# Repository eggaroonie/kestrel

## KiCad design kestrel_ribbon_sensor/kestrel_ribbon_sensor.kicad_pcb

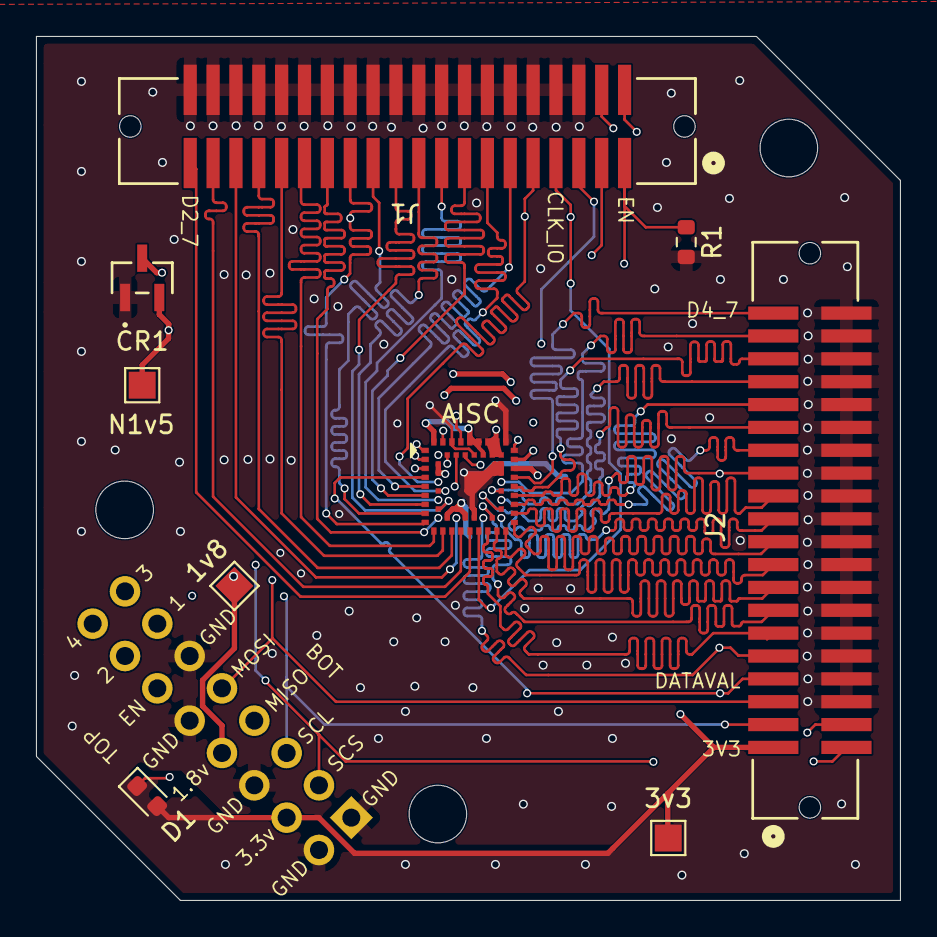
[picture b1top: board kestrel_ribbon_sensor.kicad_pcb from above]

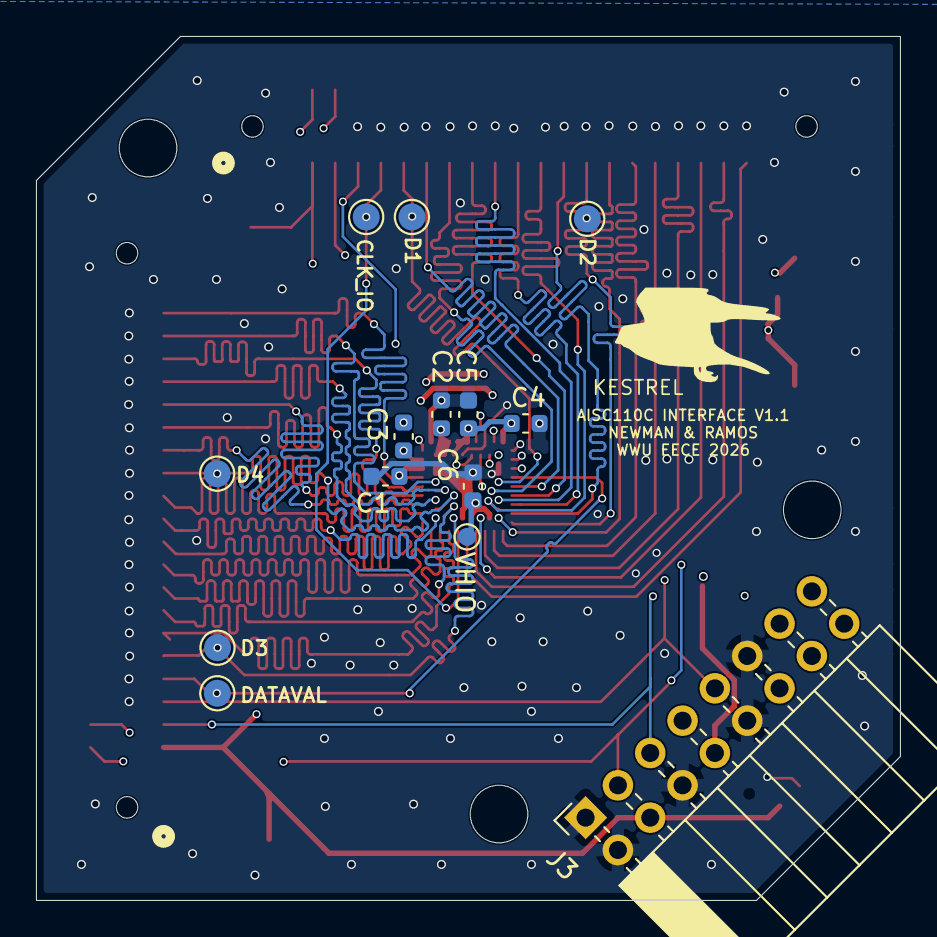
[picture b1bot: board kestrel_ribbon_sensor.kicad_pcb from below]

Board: 4 copper layers, 48.0 x 48.0 mm, 26 parts (14 on the bottom side), 51 nets.

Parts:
1v8: V1V8_PWR; TestPoint_Pad_1.5x1.5mm
3v3: V3V3_PWR; TestPoint_Pad_1.5x1.5mm
AISC: AISC110C
C1: 1uF; C_0603_1608Metric
C2, C4, C5, C6: 2.2uF; C_0603_1608Metric
C3: 220nF; C_0603_1608Metric
CLK_IO: CLK_IO; TestPoint_Pad_D1.5mm
CR1: BAS40-04-E3-08; SOT_04-HE3-08_VIS-M
D1: LED; LED_0603_1608Metric
D1#2: D1_0; TestPoint_Pad_D1.5mm
D2: D2_0; TestPoint_Pad_D1.5mm
D3: D3_0; TestPoint_Pad_D1.5mm
D4: D4_0; TestPoint_Pad_D1.5mm
DATAVAL: DATAVALID; TestPoint_Pad_D1.5mm
H1, H2, H3: MountingHole; MountingHole_3.2mm_M3
J1, J2: SHF-120-01-L-D-SM; CONN_SHF-120-01-L-D-SM_SAI
J3: DEBUG_HEADER; PinSocket_2x08_P2.54mm_Horizontal
N1v5: VN1V5_PWR; TestPoint_Pad_1.5x1.5mm
R1: 10kR; R_0603_1608Metric
VHIO: VDD_HSIO; TestPoint_Pad_D1.0mm

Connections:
/CLK_IO: AISC.23 (CLK_IO), CLK_IO.1 (1_1), J1.7
/D1_0: AISC.13 (OUT1_0), D1#2.1 (1_1), J1.9
/D1_1: AISC.5 (OUT1_1), J1.11
/D1_2: AISC.14 (OUT1_2), J1.13
/D1_3: AISC.6 (OUT1_3), J1.15
/D1_4: AISC.15 (OUT1_4), J1.17
/D1_5: AISC.7 (OUT1_5), J1.19
/D1_6: AISC.16 (OUT1_6), J1.21
/D1_7: AISC.8 (OUT1_7), J1.23
/D2_0: AISC.9 (OUT2_0), D2.1 (1_1), J1.25
/D2_1: AISC.17 (OUT2_1), J1.27
/D2_2: AISC.18 (OUT2_2), J1.29
/D2_3: AISC.19 (OUT2_3), J1.31
/D2_4: AISC.20 (OUT2_4), J1.33
/D2_5: AISC.28 (OUT2_5), J1.35
/D2_6: AISC.21 (OUT2_6), J1.37
/D2_7: AISC.22 (OUT2_7), J1.39
/D3_0: AISC.31 (OUT3_0), D3.1 (1_1), J2.9
/D3_1: AISC.24 (OUT3_1), J2.11
/D3_2: AISC.32 (OUT3_2), J2.13
/D3_3: AISC.25 (OUT3_3), J2.15
/D3_4: AISC.26 (OUT3_4), J2.17
/D3_5: AISC.33 (OUT3_5), J2.19
/D3_6: AISC.42 (OUT3_6), J2.21
/D3_7: AISC.34 (OUT3_7), J2.23
/D4_0: AISC.43 (OUT4_0), D4.1 (1_1), J2.25
/D4_1: AISC.35 (OUT4_1), J2.27
/D4_2: AISC.44 (OUT4_2), J2.29
/D4_3: AISC.36 (OUT4_3), J2.31
/D4_4: AISC.45 (OUT4_4), J2.33
/D4_5: AISC.37 (OUT4_5), J2.35
/D4_6: AISC.46 (OUT4_6), J2.37
/D4_7: AISC.38 (OUT4_7), J2.39
/DATAVAL: AISC.4 (DATAVAL), DATAVAL.1 (1_1), J2.7
/ENABLE: AISC.57 (ENABLE), J1.1, J3.12, R1.1
/GPIO1: AISC.64 (GPIO1), J1.2, J3.13
/GPIO2: AISC.63 (GPIO2), J1.3, J3.14
/GPIO3: AISC.55 (GPIO3), J1.4, J3.15
/GPIO4: AISC.62 (GPIO4), J1.5, J3.16
/SPI_CLK: AISC.3 (SPI_CLK), J2.3, J3.5
/SPI_CS: AISC.1 (~SPI_CS), J2.2, J3.3
/SPI_MISO: AISC.10 (SPI_MISO), J2.4, J3.7
/SPI_MOSI: AISC.2 (SPI_MOSI), J2.5, J3.9
/V1V8: 1v8.1 (1_1), AISC.53 (V1V8_D), AISC.54 (IMG_V1V8), AISC.58 (VDDIO), AISC.60 (V1V8), C4.1, C5.1, J3.8
/V3V3: 3v3.1 (1_1), AISC.49 (LED_V3V3), AISC.51 (V3V3), AISC.52 (V1V8_M), AISC.59 (V3V3), C2.1, D1.2 (A), J2.1, J3.4
/VDDHSIO: AISC.27 (VDDHSIO), AISC.29 (VDDHSIO), C6.1, VHIO.1 (1_1)
GND: AISC.11 (GND), AISC.12 (GND_IO), AISC.30 (GND_IO), AISC.47 (GND_IO), AISC.48 (GND), AISC.50 (LED_PGND), AISC.56 (FTM), AISC.61 (GND), C1.2, C2.2, C4.2, C5.2, C6.2, CR1.1, J1.6, J1.8, J1.10, J1.12, J1.14, J1.16, J1.18, J1.20, J1.22, J1.24, J1.26, J1.28, J1.30, J1.32, J1.34, J1.36, J1.38, J1.40, J2.6, J2.8, J2.10, J2.12, J2.14, J2.16, J2.18, J2.20, J2.22, J2.24, J2.26, J2.28, J2.30, J2.32, J2.34, J2.36, J2.38, J2.40, J3.1, J3.2, J3.6, J3.10, J3.11, R1.2
unnamed: C3.1, CR1.3
unnamed: AISC.41 (LED_K), D1.1 (K)
unnamed: AISC.40 (CP_SW), C3.2
unnamed: AISC.39 (VN1V5), C1.1, CR1.2, N1v5.1 (1_1)

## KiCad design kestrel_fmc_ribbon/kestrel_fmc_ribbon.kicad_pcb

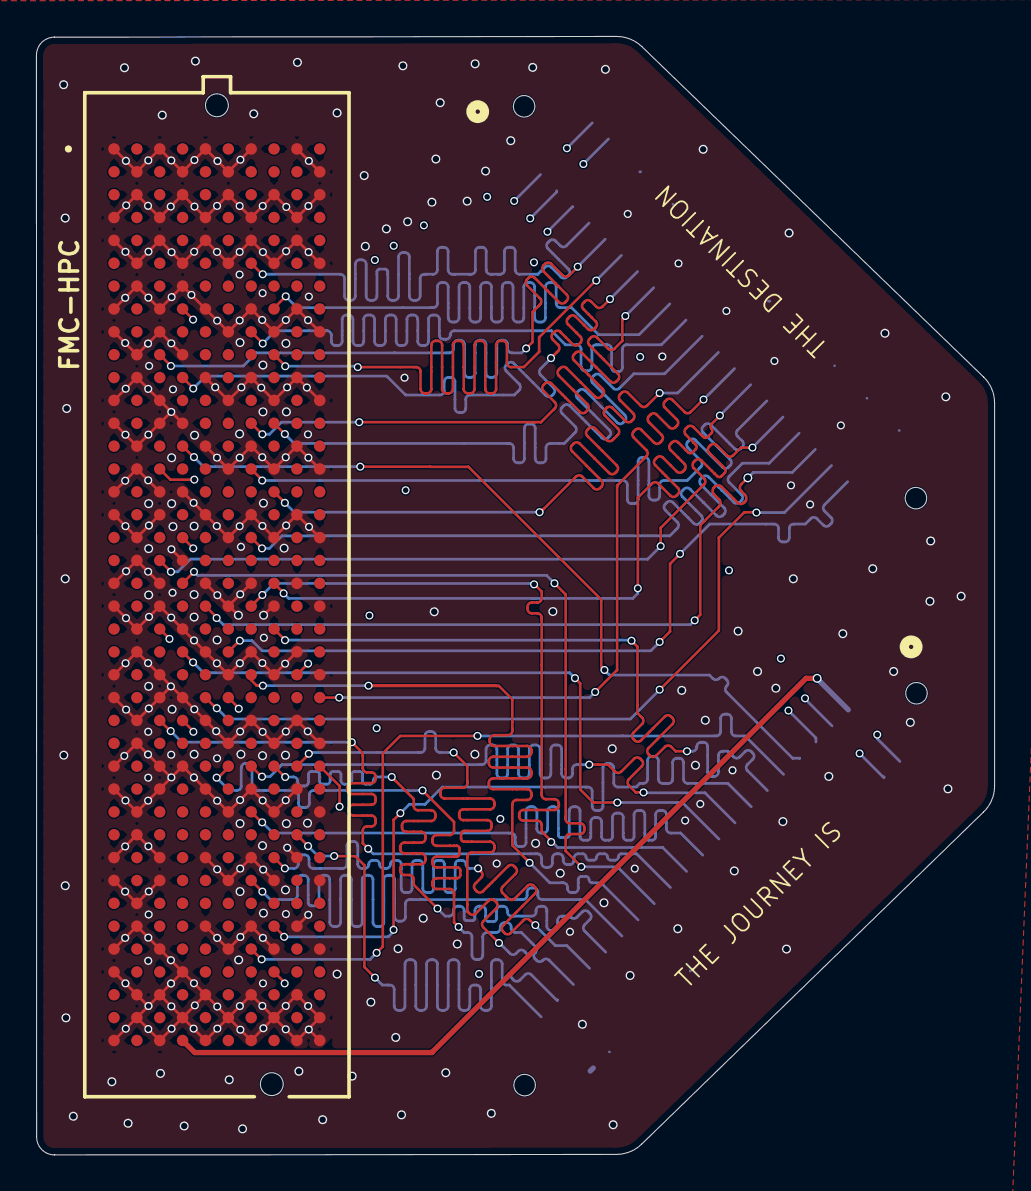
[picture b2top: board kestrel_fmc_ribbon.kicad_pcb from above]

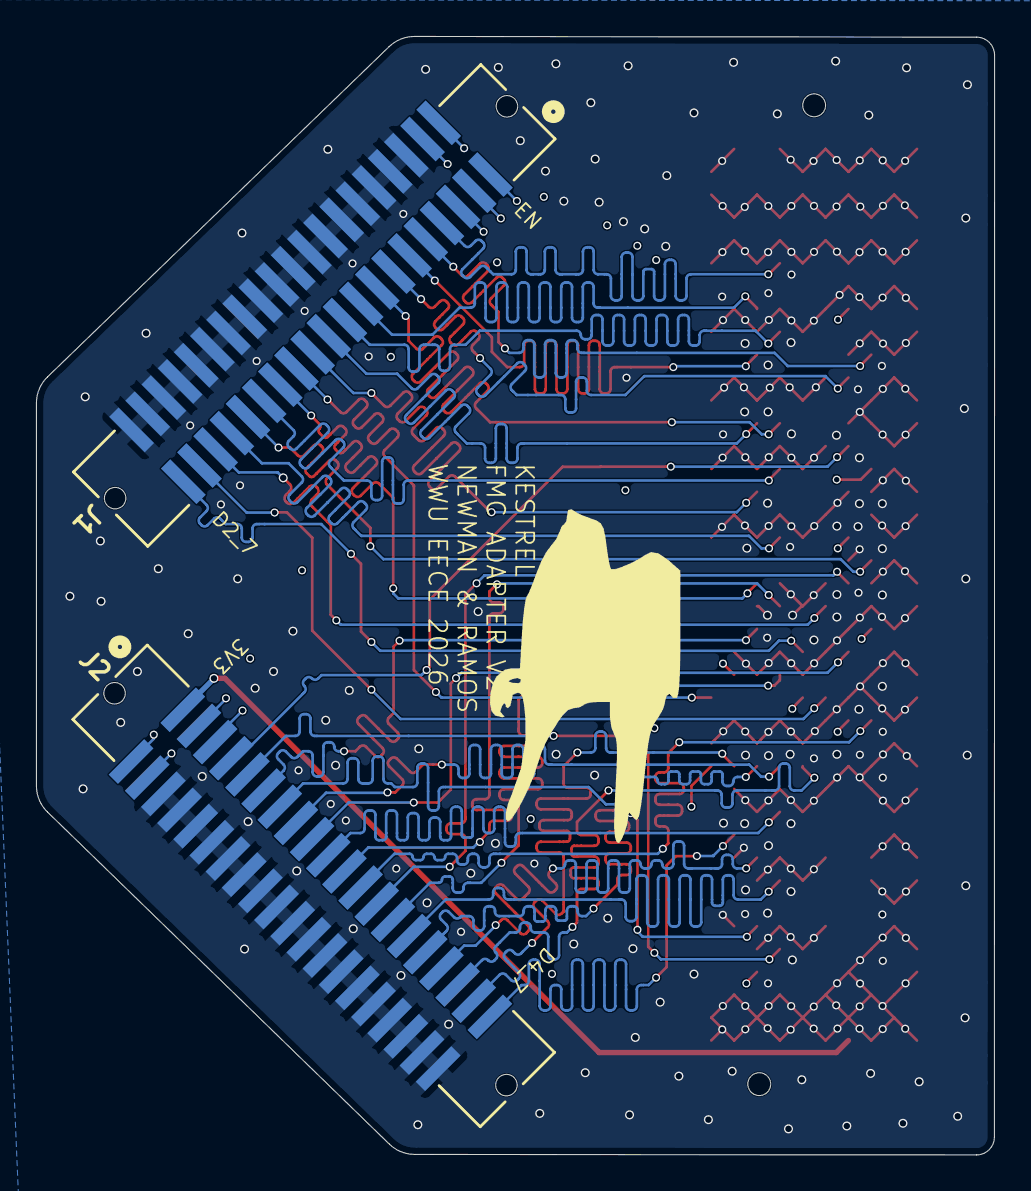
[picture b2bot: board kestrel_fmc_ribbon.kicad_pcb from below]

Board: 4 copper layers, 53.2 x 62.1 mm, 3 parts (2 on the bottom side), 45 nets.

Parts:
FMC-HPC: ASP-134602-01; SAMTEC_ASP-134602-01
J1, J2: SHF-120-01-L-D-SM; CONN_SHF-120-01-L-D-SM_SAI

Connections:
/CLK_IO: FMC-HPC.G6, J1.7
/D1_0: FMC-HPC.C10, J1.9
/D1_1: FMC-HPC.H10, J1.11
/D1_2: FMC-HPC.D11, J1.13
/D1_3: FMC-HPC.G13, J1.15
/D1_4: FMC-HPC.H8, J1.17
/D1_5: FMC-HPC.G9, J1.19
/D1_6: FMC-HPC.H13, J1.21
/D1_7: FMC-HPC.H16, J1.23
/D2_0: FMC-HPC.K25, J1.25
/D2_1: FMC-HPC.H20, J1.27
/D2_2: FMC-HPC.G15, J1.29
/D2_3: FMC-HPC.C19, J1.31
/D2_4: FMC-HPC.G18, J1.33
/D2_5: FMC-HPC.E21, J1.35
/D2_6: FMC-HPC.E25, J1.37
/D2_7: FMC-HPC.F23, J1.39
/D3_0: FMC-HPC.G36, J2.9
/D3_1: FMC-HPC.H22, J2.11
/D3_2: FMC-HPC.H35, J2.13
/D3_3: FMC-HPC.G28, J2.15
/D3_4: FMC-HPC.D23, J2.17
/D3_5: FMC-HPC.G30, J2.19
/D3_6: FMC-HPC.G21, J2.21
/D3_7: FMC-HPC.C26, J2.23
/D4_0: FMC-HPC.D20, J2.25
/D4_1: FMC-HPC.G24, J2.27
/D4_2: FMC-HPC.G33, J2.29
/D4_3: FMC-HPC.H28, J2.31
/D4_4: FMC-HPC.H32, J2.33
/D4_5: FMC-HPC.F28, J2.35
/D4_6: FMC-HPC.J28, J2.37
/D4_7: FMC-HPC.J31, J2.39
/DATAVAL: FMC-HPC.D14, J2.7
/ENABLE: FMC-HPC.C15, J1.1
/GPIO1: FMC-HPC.H37, J1.2
/GPIO2: FMC-HPC.D26, J1.3
/GPIO3: FMC-HPC.K28, J1.4
/GPIO4: FMC-HPC.C22, J1.5
/SPI_CLK: FMC-HPC.D18, J2.3
/SPI_CS: FMC-HPC.D8, J2.2
/SPI_MISO: FMC-HPC.J24, J2.4
/SPI_MOSI: FMC-HPC.F25, J2.5
/V3V3: FMC-HPC.D40, J2.1
GND: FMC-HPC.A1, FMC-HPC.A4, FMC-HPC.A5, FMC-HPC.A8, FMC-HPC.A9, FMC-HPC.A12, FMC-HPC.A13, FMC-HPC.A16, FMC-HPC.A17, FMC-HPC.A20, FMC-HPC.A21, FMC-HPC.A24, FMC-HPC.A25, FMC-HPC.A28, FMC-HPC.A29, FMC-HPC.A32, FMC-HPC.A33, FMC-HPC.A36, FMC-HPC.A37, FMC-HPC.A40, FMC-HPC.B2, FMC-HPC.B3, FMC-HPC.B6, FMC-HPC.B7, FMC-HPC.B10, FMC-HPC.B11, FMC-HPC.B14, FMC-HPC.B15, FMC-HPC.B18, FMC-HPC.B19, FMC-HPC.B22, FMC-HPC.B23, FMC-HPC.B26, FMC-HPC.B27, FMC-HPC.B30, FMC-HPC.B31, FMC-HPC.B34, FMC-HPC.B35, FMC-HPC.B38, FMC-HPC.B39, FMC-HPC.C1, FMC-HPC.C4, FMC-HPC.C5, FMC-HPC.C8, FMC-HPC.C9, FMC-HPC.C12, FMC-HPC.C13, FMC-HPC.C16, FMC-HPC.C17, FMC-HPC.C20, FMC-HPC.C21, FMC-HPC.C24, FMC-HPC.C25, FMC-HPC.C28, FMC-HPC.C29, FMC-HPC.C32, FMC-HPC.C33, FMC-HPC.C36, FMC-HPC.C38, FMC-HPC.C40, FMC-HPC.D2, FMC-HPC.D3, FMC-HPC.D6, FMC-HPC.D7, FMC-HPC.D10, FMC-HPC.D13, FMC-HPC.D16, FMC-HPC.D19, FMC-HPC.D22, FMC-HPC.D25, FMC-HPC.D28, FMC-HPC.D37, FMC-HPC.D39, FMC-HPC.E1, FMC-HPC.E4, FMC-HPC.E5, FMC-HPC.E8, FMC-HPC.E11, FMC-HPC.E14, FMC-HPC.E17, FMC-HPC.E20, FMC-HPC.E23, FMC-HPC.E26, FMC-HPC.E29, FMC-HPC.E32, FMC-HPC.E35, FMC-HPC.E38, FMC-HPC.E40, FMC-HPC.F2, FMC-HPC.F3, FMC-HPC.F6, FMC-HPC.F9, FMC-HPC.F12, FMC-HPC.F15, FMC-HPC.F18, FMC-HPC.F21, FMC-HPC.F24, FMC-HPC.F27, FMC-HPC.F30, FMC-HPC.F33, FMC-HPC.F36, FMC-HPC.F39, FMC-HPC.G1, FMC-HPC.G4, FMC-HPC.G5, FMC-HPC.G8, FMC-HPC.G11, FMC-HPC.G14, FMC-HPC.G17, FMC-HPC.G20, FMC-HPC.G23, FMC-HPC.G26, FMC-HPC.G29, FMC-HPC.G32, FMC-HPC.G35, FMC-HPC.G38, FMC-HPC.G40, FMC-HPC.H3, FMC-HPC.H6, FMC-HPC.H9, FMC-HPC.H12, FMC-HPC.H15, FMC-HPC.H18, FMC-HPC.H21, FMC-HPC.H24, FMC-HPC.H27, FMC-HPC.H30, FMC-HPC.H33, FMC-HPC.H36, FMC-HPC.H39, FMC-HPC.J1, FMC-HPC.J4, FMC-HPC.J5, FMC-HPC.J8, FMC-HPC.J11, FMC-HPC.J14, FMC-HPC.J17, FMC-HPC.J20, FMC-HPC.J23, FMC-HPC.J26, FMC-HPC.J29, FMC-HPC.J32, FMC-HPC.J35, FMC-HPC.J38, FMC-HPC.J40, FMC-HPC.K2, FMC-HPC.K3, FMC-HPC.K6, FMC-HPC.K9, FMC-HPC.K12, FMC-HPC.K15, FMC-HPC.K18, FMC-HPC.K21, FMC-HPC.K24, FMC-HPC.K27, FMC-HPC.K30, FMC-HPC.K33, FMC-HPC.K36, FMC-HPC.K39, FMC-HPC.K40, J1.6, J1.8, J1.10, J1.12, J1.14, J1.16, J1.18, J1.20, J1.22, J1.24, J1.26, J1.28, J1.30, J1.32, J1.34, J1.36, J1.38, J1.40, J2.6, J2.8, J2.10, J2.12, J2.14, J2.16, J2.18, J2.20, J2.22, J2.24, J2.26, J2.28, J2.30, J2.32, J2.34, J2.36, J2.38, J2.40

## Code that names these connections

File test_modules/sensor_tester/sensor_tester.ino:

/* AISC110C Interface Tester 
  power on & configure sensor, view image data output
  test spi communication w/ sensor
*/

#include <SPI.h>
#include "aisc110c.h"

/* pin definitions */
const int EN = 32;
const int GPIO1 = 33;
const int GPIO2 = 25;
const int GPIO3 = 26;
const int GPIO4 = 27;

const int SPI_CLK = 14;
const int SPI_SS = 15;
const int SPI_MISO = 12;
const int SPI_MOSI = 13;


void setup() {

  /* spi initialization */
  pinMode(SPI_SS, OUTPUT);
  SPI.begin(SPI_CLK, SPI_MISO, SPI_MOSI, SPI_SS);



}

void loop() {
  // put your main code here, to run repeatedly:

}

void HandleSerial(void); // serial interface for config & start/stop

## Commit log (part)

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2026-05-09 Update LICENSE
2026-05-19 added some newlines to hopefully make this more readable
2026-05-19 undoing that.. maybe giving it a filetype was enough to make it work
2026-05-19 initialize project
2026-05-23 sensor pcb setup
    creates kicad project for AISC110C sensor breakout board
2026-05-23 beginning setup for aisc110c sensor ic
2026-06-15 aisc110c fmc-hpc board schematic - revision 1
